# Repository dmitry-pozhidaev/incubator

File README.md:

# incubator
Инкубатор для кибернетического выведения птенцов кур

Поделка выполнена на базе микроконтроллера STM32L011

Контроль температуры на DS1820 

Основная логика реализована посредством Дракона http://drakon-editor.sourceforge.net

Механический привод для вращения яиц сделан в Поднебесной. Ссылка на привод киберкурицы: https://aliexpress.ru/item/1005001309305247.html

pcb/eagle - принципиальная схема и печатная плата в формате Eagle

pcb/gcode - нарезка печатной платы на чпу станке. 

Используемая фреза 0.1 мм https://aliexpress.ru/item/4000966103866.html 

Станок для нарезки печатной платы https://aliexpress.ru/item/4000296585604.html

Разрешаю гражданам Великой России свободное копирование, воспроизведение и промышленное изготовление данного устройства без любых финансовых отчислений автору.
Иными представителям цивилизаций планеты Земля копирование, воспроизведение и любое промышленное или кустарное изготовление всенеприменно должно согласовываться с автором данного произведения.

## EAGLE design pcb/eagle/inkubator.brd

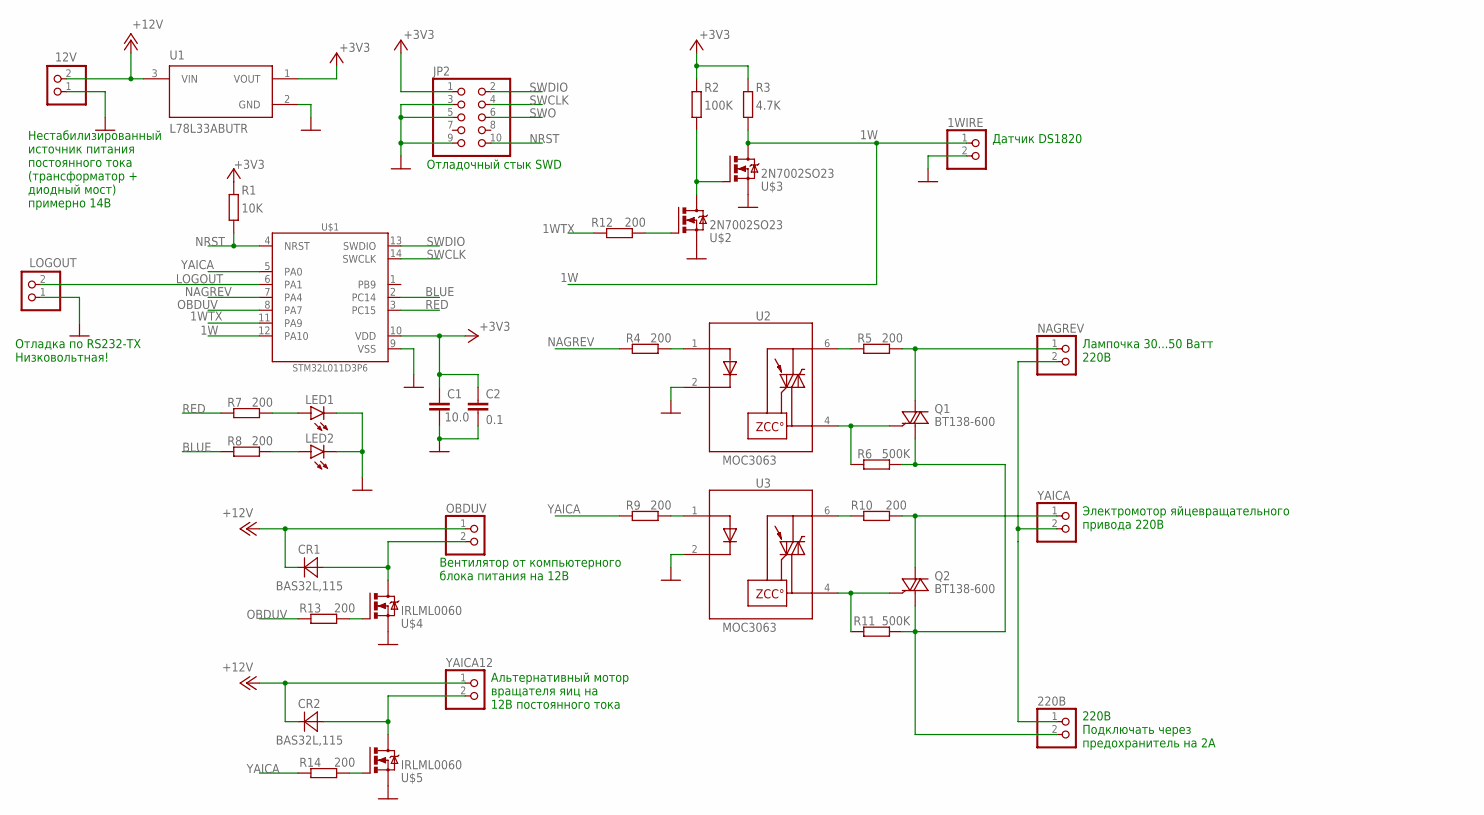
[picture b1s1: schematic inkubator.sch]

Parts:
1WIRE, 12V, 220В: PINHD-1X2; 1X02
C1: 10.0; C1206
C2: 0.1; C1206
CR1, CR2: BAS32L,115; SOD80C
JP2: PINHD-2X5; 2X05
LED1, LED2: LED10MM
LOGOUT: PINHD-1X2; 1X02
NAGREV: PINHD-1X2; 1X02
OBDUV: PINHD-1X2; 1X02
Q1, Q2: BT138-600; DPAK
R1: 10K; R0603
R2: 100K; R0603
R3: 4.7K; R0603
R4, R7, R8, R9, R12, R13, R14: 200; R0603
R5, R10: 200; R1206
R6, R11: 500K; R1206
U1: L78L33ABUTR; VREG_L78L12ABUTR
U2, U3: MOC3063; SOIC254P1030X460-6N
U$1: STM32L011D3P6; SOP65P640X120-14N
U$2, U$3: 2N7002SO23; SOT23
U$4, U$5: IRLML0060; SOT23
YAICA, YAICA12: PINHD-1X2; 1X02

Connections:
1W: 1WIRE.1, R3.1, U$1.12 (PA10), U$3.3 (D)
1WTX: R12.2, U$1.11 (PA9)
+3V3: C1.1, C2.1, JP2.1, R1.2, R2.2, R3.2, U1.1 (VOUT), U$1.10 (VDD)
+12V: 12V.2, CR1.1 (CATHODE), CR2.1 (CATHODE), OBDUV.1, U1.3 (VIN), YAICA12.1
BLUE: R8.2, U$1.2 (PC14)
GND: 1WIRE.2, 12V.1, C1.2, C2.2, JP2.3, JP2.5, JP2.9, LED1.K (C), LED2.K (C), LOGOUT.1, U1.2 (GND), U2.2 (C), U3.2 (C), U$1.9 (VSS), U$2.2 (S), U$3.2 (S), U$4.2 (S), U$5.2 (S)
LOGOUT: LOGOUT.2, U$1.6 (PA1)
unnamed: R2.1, U$2.3 (D), U$3.1 (G)
unnamed: R4.1, U2.1 (A)
unnamed: Q1.3 (G), R6.2, U2.4 (MT1)
unnamed: R5.2, U2.6 (MT2)
unnamed: NAGREV.1, Q1.2 (A2), R5.1
unnamed: 220В.1, NAGREV.2, YAICA.2
unnamed: R9.1, U3.1 (A)
unnamed: Q2.3 (G), R11.2, U3.4 (MT1)
unnamed: LED1.A, R7.1
unnamed: LED2.A, R8.1
unnamed: R10.2, U3.6 (MT2)
unnamed: Q2.2 (A2), R10.1, YAICA.1
unnamed: 220В.2, Q1.1 (A1), Q2.1 (A1), R6.1, R11.1
unnamed: R12.1, U$2.1 (G)
unnamed: R13.1, U$4.1 (G)
unnamed: CR1.2 (ANODE), OBDUV.2, U$4.3 (D)
unnamed: R14.1, U$5.1 (G)
unnamed: CR2.2 (ANODE), U$5.3 (D), YAICA12.2
NAGREV: R4.2, U$1.7 (PA4)
NRST: JP2.10, R1.1, U$1.4 (NRST)
OBDUV: R13.2, U$1.8 (PA7)
RED: R7.2, U$1.3 (PC15)
SWCLK: JP2.4, U$1.14 (SWCLK)
SWDIO: JP2.2, U$1.13 (SWDIO)
SWO: JP2.6
YAICA: R9.2, R14.2, U$1.5 (PA0)

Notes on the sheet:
Лампочка 30...50 Ватт 220В
Электромотор яйцевращательного привода 220В
Датчик DS1820
Вентилятор от компьютерного блока питания на 12В
Отладка по RS232-TX Низковольтная!
Нестабилизированный источник питания постоянного тока (трансформатор + диодный мост) примерно 14В
Отладочный стык SWD
220В Подключать через предохранитель на 2А
Альтернативный мотор вращателя яиц на 12В постоянного тока

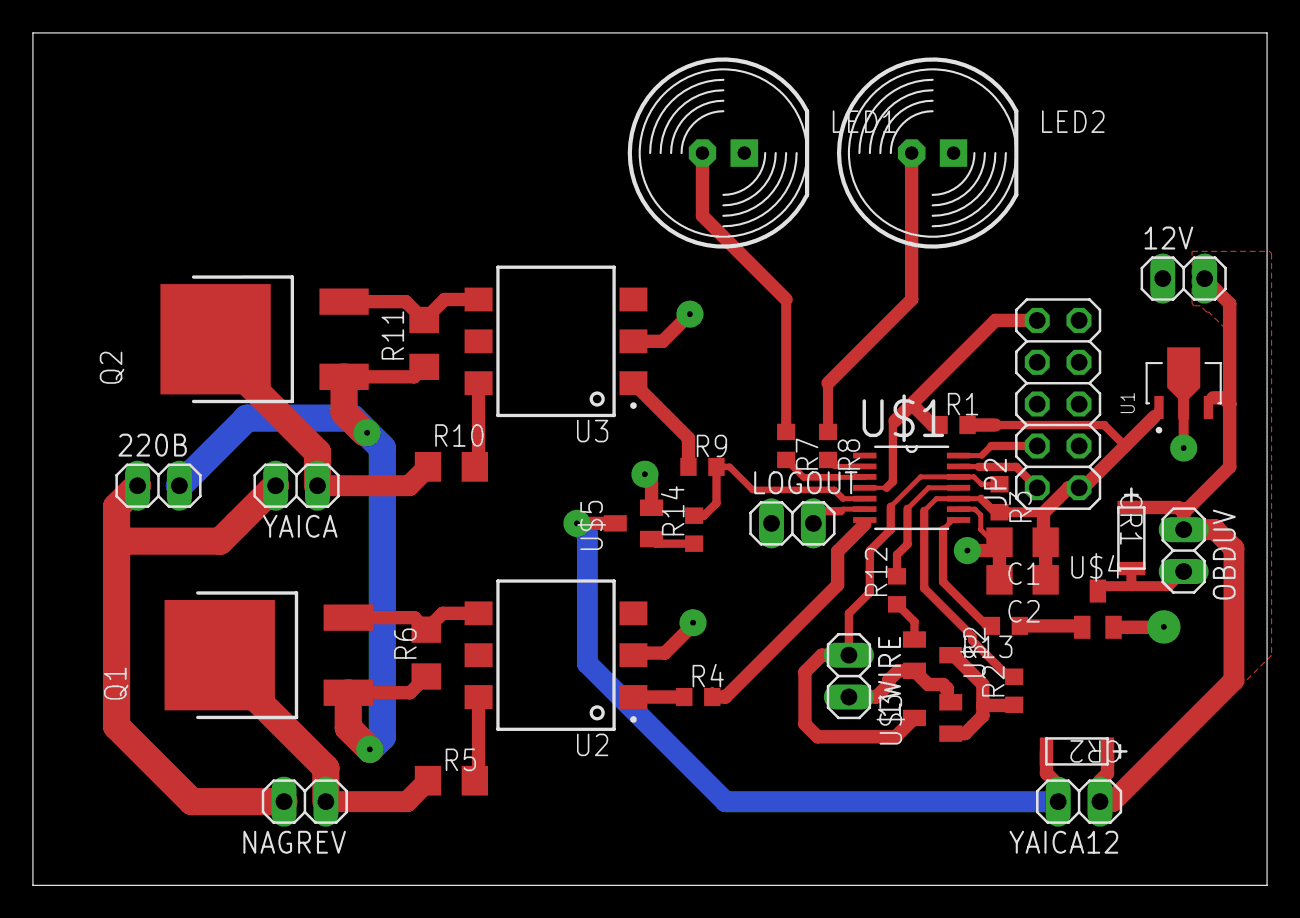
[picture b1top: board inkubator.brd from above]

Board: 2 copper layers, 74.9 x 51.7 mm, 39 parts (0 on the bottom side), 32 nets.

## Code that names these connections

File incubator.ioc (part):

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Mcu.Name=STM32L011D(3-4)Px
Mcu.Package=TSSOP14
Mcu.UserName=STM32L011D3Px
PA1.Mode=Half_duplex(single_wire_mode)
PA1.Signal=LPUART1_TX
PA10.Mode=Asynchronous
PA10.Signal=USART2_RX
PA13.Mode=Serial_Wire
PA13.Signal=SYS_SWDIO
PA14.Mode=Serial_Wire
PA14.Signal=SYS_SWCLK
PA4.GPIOParameters=GPIO_PuPd,GPIO_Label
PA4.GPIO_Label=OBDUV
PA4.GPIO_PuPd=GPIO_PULLUP
PA4.Signal=GPIO_Output
PA7.GPIOParameters=GPIO_PuPd,GPIO_Label
PA7.GPIO_Label=NAGREV
PA7.GPIO_PuPd=GPIO_PULLUP
PA7.Signal=GPIO_Output
PA9.Mode=Asynchronous
PA9.Signal=USART2_TX
PC14-OSC32_IN.GPIOParameters=GPIO_PuPd,GPIO_Label,GPIO_ModeDefaultOutputPP
PC14-OSC32_IN.GPIO_Label=BLUE
PC14-OSC32_IN.GPIO_ModeDefaultOutputPP=GPIO_MODE_OUTPUT_PP
PC14-OSC32_IN.GPIO_PuPd=GPIO_PULLDOWN
PC14-OSC32_IN.Signal=GPIO_Output
PC15-OSC32_OUT.GPIOParameters=GPIO_PuPd,GPIO_Label,GPIO_ModeDefaultOutputPP
PC15-OSC32_OUT.GPIO_Label=RED
PC15-OSC32_OUT.GPIO_ModeDefaultOutputPP=GPIO_MODE_OUTPUT_PP
PC15-OSC32_OUT.GPIO_PuPd=GPIO_PULLDOWN
PC15-OSC32_OUT.Signal=GPIO_Output
RCC.HSE_VALUE=8000000
RCC.SYSCLKFreq_VALUE=24000000
RCC.SYSCLKSource=RCC_SYSCLKSOURCE_PLLCLK
board=custom

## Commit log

2022-02-20 begin
2022-02-20 Добавлена схема и недоделанная плата
2022-02-20 пустой проект Дракона добавлен
2022-02-20 Первая версия печатной платы
2022-02-20 Рефакторинг печатной платы
2022-02-20 Рефакторинг принципиальной схемы и печатной платы
2022-02-20 Добавлен узел управления 12-и вольтовым мотором привода яйцекрутилки, для случая если мотор DC 12V
2022-02-20 Рефакторинг сетевой разводки
